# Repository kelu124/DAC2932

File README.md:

# DAC2932

DAC2932 devboard

## Objective

```
TLDR: Getting a fast DAC board controlled without any FPGA, purely fast, simple, open source hardware (rp2040).

Outputs:
* 2x 40Msps, 12bits signal (I-DACs)
* 4x 1Msps, 12bits (V-DAC) (not really 4x1Msps but good enough description)
```

The [DAC2932 devboard](https://github.com/kelu124/DAC2932) is a simple yet powerful tool for anyone working with high-speed digital-to-analog conversion (DAC). Designed for ease of use, it combines a high dynamic range with low power consumption, making it a great choice for engineers and hobbyists alike.

At its core, the DAC2932 features dual 12-bit DACs capable of delivering up to 40 million samples per second (MSPS), as well as four additional voltage-output DACs operating at around 1 MSPS. The entire setup is controlled by a Raspberry Pi Pico (RP2040), meaning you don’t need any complex FPGA programming. The open-source toolchain makes it accessible and versatile.

You get fast, accurate signal output with minimal hassle, ideal for prototyping or integrating into larger systems. Whether you’re working on emulating ultrasound signals, as I am, or experimenting with other real-time applications, the DAC2932 devboard offers a user-friendly way to get high-speed DAC performance without the headaches of advanced hardware setups. 

## Software

* Everything in `/software/` using classical rp2040 toolchain.

## Hardware

* Everything in `/hardware/` using classical KiCad.

# Also

## License

This work is based on a previous TAPR project, [the echOmods project](https://github.com/kelu124/echomods/), the [un0rick project](https://github.com/kelu124/un0rick) and more recently the gamind-card, pmod-enabled format [pic0rick](https://github.com/kelu124/pic0rick/) family. Its boards are open hardware and software, developped with open-source elements.

Copyright Luc Jonveaux (kelu124@gmail.com) 2024

* The *hardware* is licensed under TAPR Open Hardware License (www.tapr.org/OHL)
* The *software* components are free software: you can redistribute it and/or modify it under the terms of the GNU General Public License as published by the Free Software Foundation, either version 3 of the License, or (at your option) any later version.
* The *documentation* is licensed under a [Creative Commons Attribution-ShareAlike 3.0 Unported License](http://creativecommons.org/licenses/by-sa/3.0/).

## Disclaimer(s)

This project is distributed WITHOUT ANY EXPRESS OR IMPLIED WARRANTY, INCLUDING OF MERCHANTABILITY, SATISFACTORY QUALITY AND FITNESS FOR A PARTICULAR PURPOSE. 

See the GNU General Public License for more details.

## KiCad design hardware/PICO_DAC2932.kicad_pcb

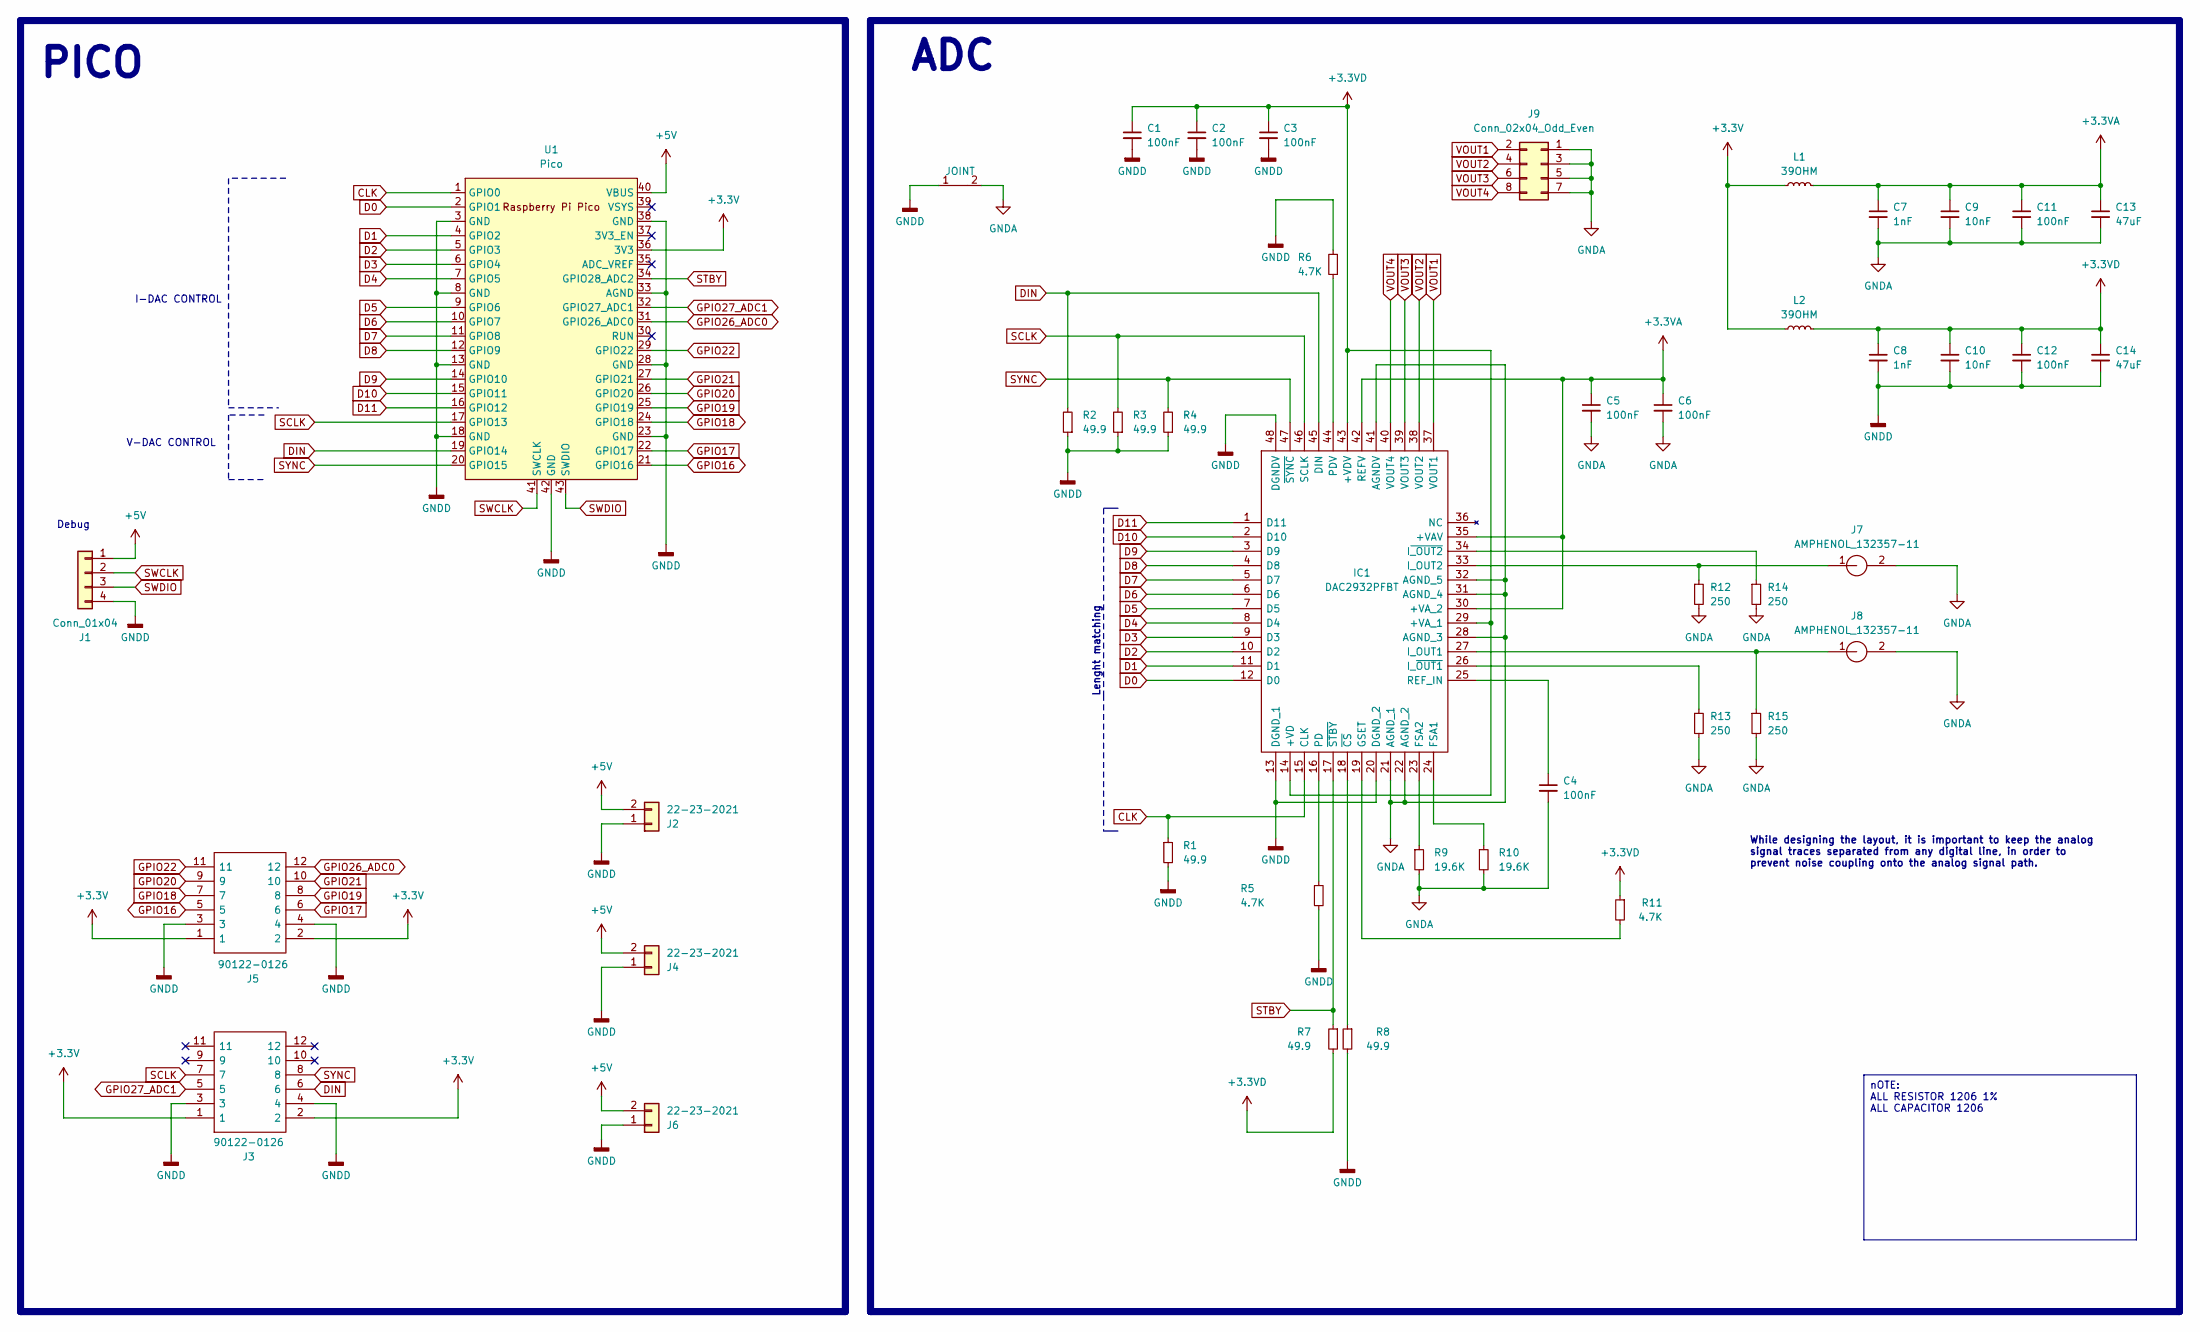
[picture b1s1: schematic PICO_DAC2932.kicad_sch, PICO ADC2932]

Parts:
C1, C2, C3, C4, C5, C6, C11, C12: 100nF; C_1206_3216Metric
C7, C8: 1nF; C_1206_3216Metric
C9, C10: 10nF; C_1206_3216Metric
C13, C14: 47uF; C_1206_3216Metric
IC1: DAC2932PFBT; QFP50P900X900X120-48N; Mouser Part Number 595-DAC2932PFBT
J1: Conn_01x04; PinHeader_1x04_P2.54mm_Vertical
J2, J4, J6: 22-23-2021; PinHeader_1x02_P2.54mm_Vertical; MPN 22-23-2021
J3, J5: 90122-0126; PinSocket_2x06_P2.54mm_Horizontal; Mouser Part Number 710-613012243121
J7, J8: AMPHENOL_132357-11; Mouser Part Number 530-142-0701-801
J9: Conn_02x04_Odd_Even; PinHeader_2x04_P2.54mm_Vertical
JO1: JOINT
L1, L2: 39OHM; L_1206_3216Metric; Tolerance 1%
R1, R2, R3, R4, R7, R8: 49.9; R_1206_3216Metric; Tolerance 1%
R5, R6, R11: 4.7K; R_1206_3216Metric; Tolerance 1%
R9, R10: 19.6K; R_1206_3216Metric; Tolerance 1%
R12, R13, R14, R15: 250; R_1206_3216Metric; Tolerance 1%
U1: Pico; RPi_Pico_SMD; MPN Pico

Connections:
+3.3V: J3.1, J3.2, J5.1, J5.2, L1.1, L2.1, U1.36 (3V3)
+3.3VA: C5.1, C6.1, C7.1, C9.1, C11.1, C13.1, IC1.30 (+VA_2), IC1.35 (+VAV), IC1.42 (REFV), L1.2
+3.3VD: C1.1, C2.1, C3.1, C8.1, C10.1, C12.1, C14.1, IC1.14 (+VD), IC1.29 (+VA_1), IC1.43 (+VDV), L2.2, R7.2, R11.1
+5V: J1.1, J2.2, J4.2, J6.2, U1.40 (VBUS)
CLK: IC1.15 (CLK), R1.1, U1.1 (GPIO0)
D0: IC1.12 (D0), U1.2 (GPIO1)
D1: IC1.11 (D1), U1.4 (GPIO2)
D2: IC1.10 (D2), U1.5 (GPIO3)
D3: IC1.9 (D3), U1.6 (GPIO4)
D4: IC1.8 (D4), U1.7 (GPIO5)
D5: IC1.7 (D5), U1.9 (GPIO6)
D6: IC1.6 (D6), U1.10 (GPIO7)
D7: IC1.5 (D7), U1.11 (GPIO8)
D8: IC1.4 (D8), U1.12 (GPIO9)
D9: IC1.3 (D9), U1.14 (GPIO10)
D10: IC1.2 (D10), U1.15 (GPIO11)
D11: IC1.1 (D11), U1.16 (GPIO12)
DIN: IC1.45 (DIN), J3.6, R2.2, U1.19 (GPIO14)
GNDA: C4.2, C5.2, C6.2, C7.2, C9.2, C11.2, C13.2, IC1.21 (AGND_1), IC1.22 (AGND_2), IC1.28 (AGND_3), IC1.31 (AGND_4), IC1.32 (AGND_5), IC1.41 (AGNDV), J7.2, J8.2, J9.1, J9.3, J9.5, J9.7, JO1.2, R9.2, R10.2, R12.2, R13.2, R14.2, R15.2
GNDD: C1.2, C2.2, C3.2, C8.2, C10.2, C12.2, C14.2, IC1.13 (DGND_1), IC1.20 (DGND_2), IC1.48 (DGNDV), J1.4, J2.1, J3.3, J3.4, J4.1, J5.3, J5.4, J6.1, JO1.1, R1.2, R2.1, R3.1, R4.1, R5.2, R6.2, R8.2, U1.3 (GND), U1.8 (GND), U1.13 (GND), U1.18 (GND), U1.23 (GND), U1.28 (GND), U1.33 (AGND), U1.38 (GND), U1.42 (GND)
GPIO16: J5.5, U1.21 (GPIO16)
GPIO17: J5.6, U1.22 (GPIO17)
GPIO18: J5.7, U1.24 (GPIO18)
GPIO19: J5.8, U1.25 (GPIO19)
GPIO20: J5.9, U1.26 (GPIO20)
GPIO21: J5.10, U1.27 (GPIO21)
GPIO22: J5.11, U1.29 (GPIO22)
GPIO26_ADC0: J5.12, U1.31 (GPIO26_ADC0)
GPIO27_ADC1: J3.5, U1.32 (GPIO27_ADC1)
unnamed: IC1.24 (FSA1), R10.1
unnamed: IC1.23 (FSA2), R9.1
unnamed: IC1.19 (GSET), R11.2
unnamed: IC1.27 (I_OUT1), J8.1, R15.1
unnamed: IC1.33 (I_OUT2), J7.1, R12.1
unnamed: IC1.26 (I_~OUT1), R13.1
unnamed: IC1.34 (I~_OUT2), R14.1
unnamed: IC1.16 (PD), R5.1
unnamed: IC1.44 (PDV), R6.1
unnamed: C4.1, IC1.25 (REF_IN)
unnamed: IC1.18 (~CS), R8.1
SCLK: IC1.46 (SCLK), J3.7, R3.2, U1.17 (GPIO13)
STBY: IC1.17 (~STBY), R7.1, U1.34 (GPIO28_ADC2)
SWCLK: J1.2, U1.41 (SWCLK)
SWDIO: J1.3, U1.43 (SWDIO)
SYNC: IC1.47 (~SYNC), J3.8, R4.2, U1.20 (GPIO15)
VOUT1: IC1.37 (VOUT1), J9.2
VOUT2: IC1.38 (VOUT2), J9.4
VOUT3: IC1.39 (VOUT3), J9.6
VOUT4: IC1.40 (VOUT4), J9.8

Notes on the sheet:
nOTE: ALL RESISTOR 1206 1% ALL CAPACITOR 1206
While designing the layout, it is important to keep the analog signal traces separated from any digital line, in order to prevent noise coupling onto the analog signal path.
ADC
Lenght matching
V-DAC CONTROL
PICO
Debug
I-DAC CONTROL

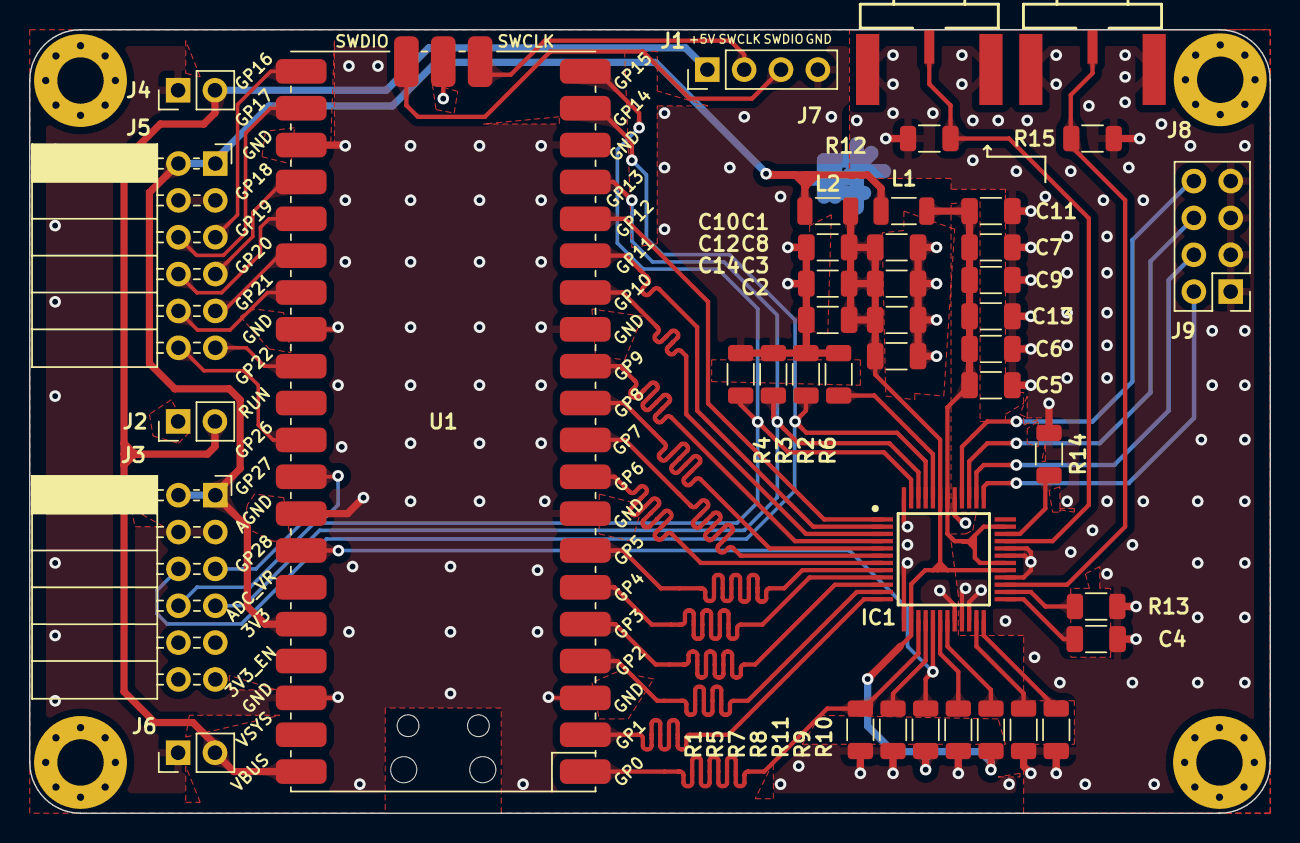
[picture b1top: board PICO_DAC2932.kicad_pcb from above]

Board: 2 copper layers, 85.5 x 54.0 mm, 43 parts (1 on the bottom side), 49 nets.

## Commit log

2024-09-25 Initial release
2024-09-26 autoupdate
